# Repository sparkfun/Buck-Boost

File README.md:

SparkFun Buck-Boost Converter
========================================

[*SparkFun Buck-Boost Converter (15208)*](https://www.sparkfun.com/products/15208)

<Basic description of the part.>

Repository Contents
-------------------

* **/Hardware** - Eagle design files (.brd, .sch)

Documentation
--------------
* **[Hookup Guide](https://learn.sparkfun.com/tutorials/buck-boost-hookup-guide)** - Basic hookup guide for the SparkFun Buck-Boost Converter.

License Information
-------------------

This product is _**open source**_!

Please review the LICENSE.md file for license information.

If you have any questions or concerns on licensing, please contact technical support on our [SparkFun forums](https://forum.sparkfun.com/viewforum.php?f=152).

Distributed as-is; no warranty is given.

- Your friends at SparkFun.

_<COLLABORATION CREDIT>_

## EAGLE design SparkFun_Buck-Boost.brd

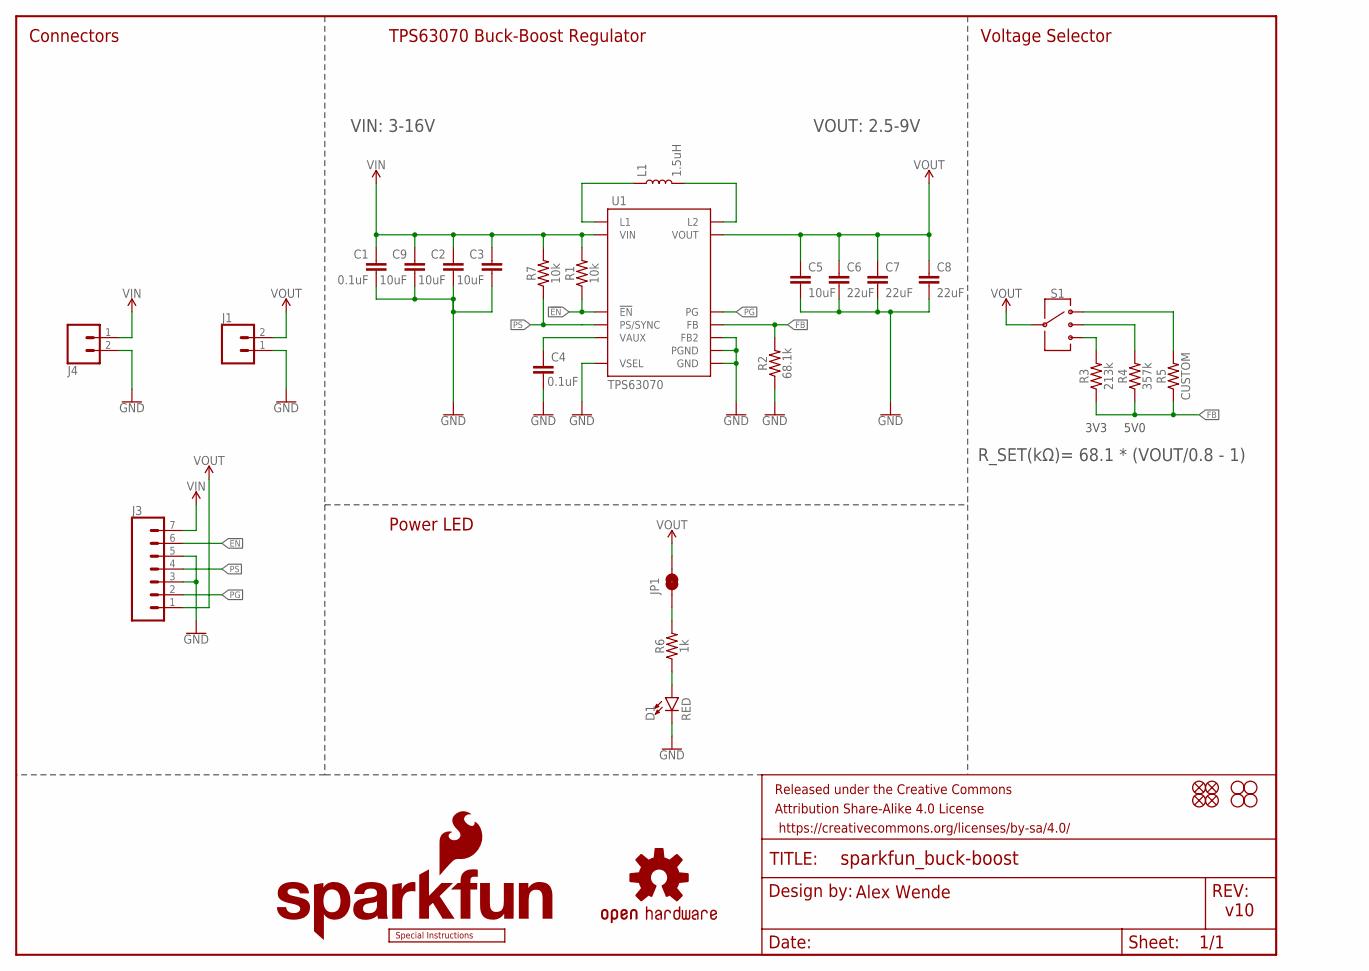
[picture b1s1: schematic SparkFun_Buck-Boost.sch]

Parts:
C1, C4: 0.1uF; 0603
C2, C3, C5, C9: 10uF; 0805
C6, C7, C8: 22uF; 0805
D1: RED; LED-0603
FD1, FD2, FD3, FD4: FIDUCIALUFIDUCIAL; FIDUCIAL-MICRO
FRAME1: FRAME-LETTER; CREATIVE_COMMONS
H1, H2, H3, H4: STAND-OFF
J1, J4: CONN_023.5MM-NO_SILK; SCREWTERMINAL-3.5MM-2-NS
J3: CONN_07NO_SILK; 1X07_NO_SILK
JP1: JUMPER-SMT_2_NC_TRACE_NO-SILK; SMT-JUMPER_2_NC_TRACE_NO-SILK
L1: 1.5uH; XFL4020
LOGO1: SFE_LOGO_NAME_FLAME.1_INCH; SFE_LOGO_NAME_FLAME_.1
LOGO2: OSHW-LOGOS; OSHW-LOGO-S
LOGO3: SPECIAL_INSTRUCTIONS-ORDERING; ORDERING_INSTRUCTIONS
R1, R7: 10k; 0603
R2: 68.1k; 0603
R3: 213k; 0603
R4: 357k; 0603
R5: CUSTOM; AXIAL-0.3
R6: 1k; 0603
S1: SWITCH-SP3T-SMD; SWITCH_SP3T_SMD
U1: TPS63070; VQFN-15-HR(3X2.5)

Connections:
!EN: J3.6, R1.1, U1.P$14 (!EN)
FB: R2.2, R3.1, R4.1, R5.P$1 (1), U1.P$5 (FB)
GND: C1.2, C2.2, C3.2, C4.2, C5.2, C6.2, C7.2, C8.2, C9.2, D1.C, J1.1, J3.3, J3.5, J4.2, R2.1, U1.P$4 (GND), U1.P$6 (FB2), U1.P$10 (PGND), U1.P$15 (VSEL)
unnamed: L1.P$1 (1), U1.P$11 (L1)
unnamed: L1.P$2 (2), U1.P$9 (L2)
unnamed: R5.P$2 (2), S1.1
unnamed: R4.2, S1.2
unnamed: C4.1, U1.P$3 (VAUX)
unnamed: R3.2, S1.4
unnamed: JP1.1, R6.2
unnamed: D1.A, R6.1
PG: J3.2, U1.P$2 (PG)
PS: J3.4, R7.1, U1.P$1 (PS/SYNC)
VIN: C1.1, C2.1, C3.1, C9.1, J3.7, J4.1, R1.2, R7.2, U1.P$12/13 (VIN)
VOUT: C5.1, C6.1, C7.1, C8.1, J1.2, J3.1, JP1.2, S1.3, U1.P$7/8 (VOUT)

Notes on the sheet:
v10
Alex Wende
Connectors
TPS63070 Buck-Boost Regulator
Voltage Selector
VIN: 3-16V
VOUT: 2.5-9V
R_SET(kΩ)= 68.1 * (VOUT/0.8 - 1)
Power LED
3V3
5V0

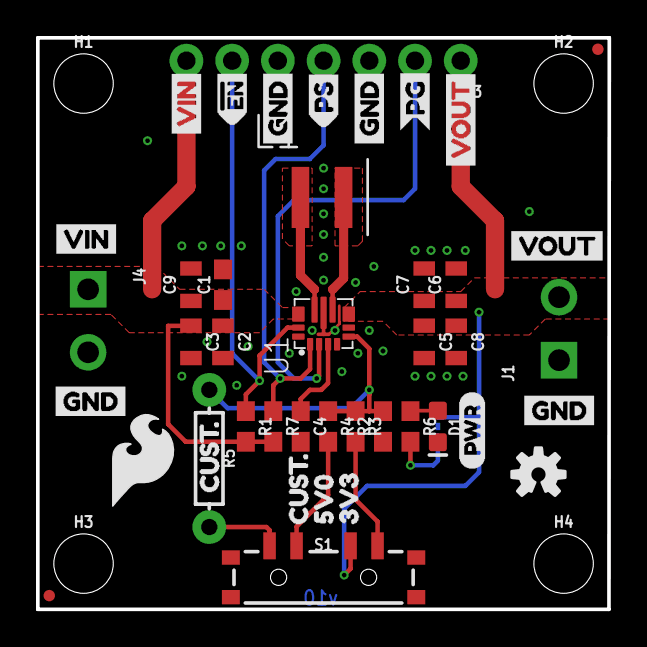
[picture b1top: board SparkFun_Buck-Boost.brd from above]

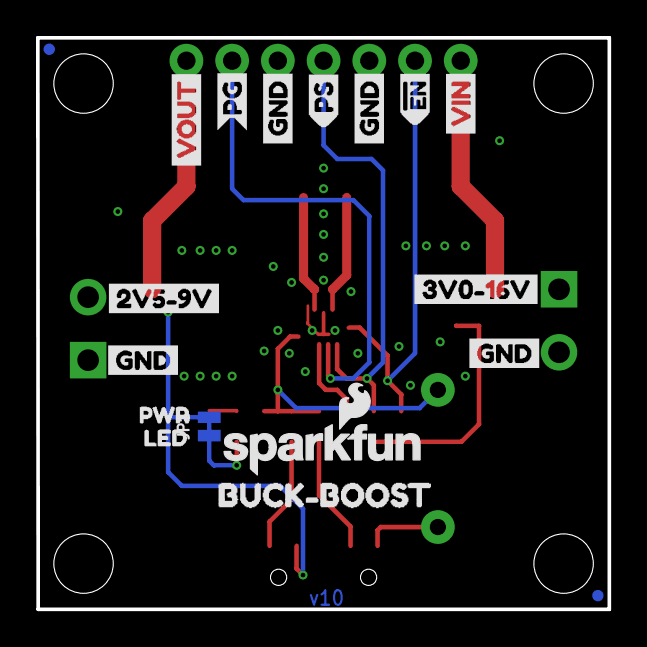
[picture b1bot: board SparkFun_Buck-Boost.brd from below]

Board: 2 copper layers, 31.8 x 31.8 mm, 67 parts (18 on the bottom side), 15 nets.

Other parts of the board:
U$1: PWR2
U$2, U$17: CUST#7
U$3, U$25: VIN0
U$4, U$20, U$30, U$31: GND1
U$5: VIN3
U$6, U$7, U$12, U$13: GND4
U$8: VOUT5
U$9: SFE_LOGO_FLAME_.2
U$10: 3V0#16V6
U$11: PWR1
U$14: 2V5#9V1
U$15: BUCK#BOOST18
U$16: LED0
U$18: 5V08
U$19: 3V39
U$21, U$26: VOUT2
U$22, U$28: #EN0
U$23, U$29: PS1
U$24, U$27: PG2

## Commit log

2019-01-30 Design Review Changes
    -Moved standoffs 0.1" offset
    -Added power LED with jumper to output
    -Added vias under IC1
    -Added units to measures layer
2019-01-30 QC Fixes
    -Fixed board dimention width
    -Fixed feedback resistor equation
    -Adjusted power led silk
    -Adjusted VIN copper pour to line up with C1 tstop
2019-03-29 V10 changes
    - Added note for 2oz copper
    - Replace power connections with 3.5mm screw terminals
2019-04-03 Updated BOM
    Replaced 357k resistor with 365k resistor
2019-04-29 Formatting repo

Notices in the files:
parts and their libraries:
SparkFun-Aesthetics: Licensing: Creative Commons ShareAlike 4.0 International - https://creativecommons.org/licenses/by-sa/4.0
SparkFun-Aesthetics: Released under the Creative Commons Attribution Share-Alike 4.0 License
SparkFun-Aesthetics: https://creativecommons.org/licenses/by-sa/4.0
